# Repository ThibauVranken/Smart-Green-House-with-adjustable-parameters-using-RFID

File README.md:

# Smart-Green-House-with-adjustable-parameters-using-RFID

In this project, you will see how to make your own smart greenhouse with customisable parameters using RFID. The measured sensor values are nicely displayed in a Grafana dashboard via a Grafana server.  You can use this in the industry, for example, to reduce costs in terms of actuator energy or to get a better picture of the situation your plants are in. This way, the plants will always have the ideal environment so they grow faster and healthier.

Folder ‘Documentation + tutorial’:
All hardware and software are in the document ‘Documentatie Serre’ and the explanation to set up a Grafana server is in the document ‘Grafana server’.

Folder ‘Code’:
The code for the ESP32 and the RaspberryPi (MQTT - InfluxDB bridge) are both in this folder.

Folder ‘PCB’:
Here you will find the electronic schematic and pcb design. For more explanation of the circuits, please see ‘Documentatie Serre’.

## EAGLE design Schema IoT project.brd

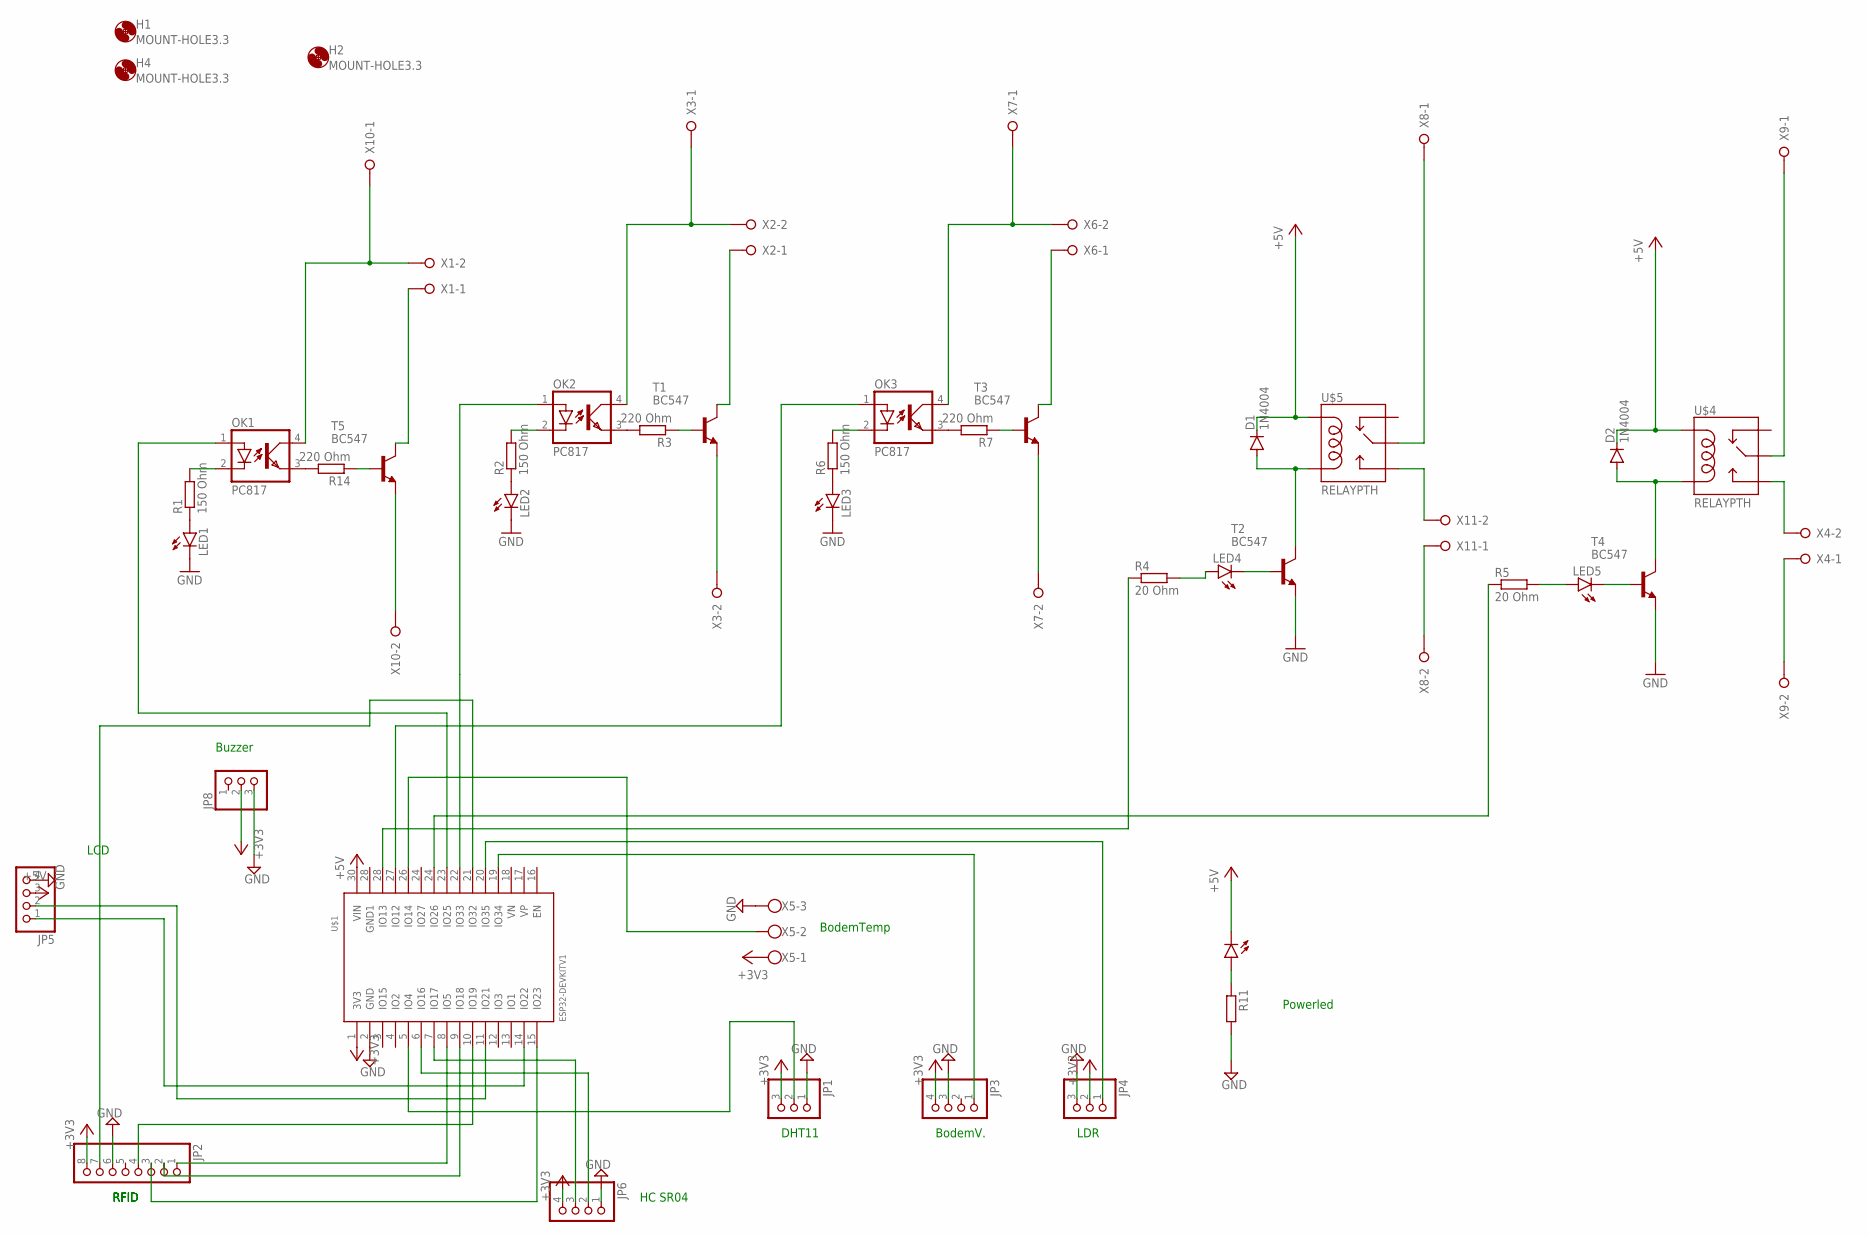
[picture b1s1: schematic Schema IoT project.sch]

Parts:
D1, D2: 1N4004; DO41-10
H1, H2, H4: MOUNT-HOLE3.3; 3,3
JP1, JP4, JP8: PINHD-1X3; 1X03
JP2: PINHD-1X8; 1X08
JP3, JP5, JP6: PINHD-1X4; 1X04
LED1, LED2, LED3, LED4, LED5: LED5MM
OK1, OK2, OK3: PC817; DIL04
PWRLEDRASPBERRYPI2: LED5MM
R1, R2, R6: 150 Ohm; 0207/10
R3, R7, R14: 220 Ohm; 0207/10
R4, R5: 20 Ohm; 0207/10
R11: R-EU_0207/10; 0207/10
T1, T2, T3, T4, T5: BC547; TO92
U$1: ESP32DEVKITV1; ESP32-DEVKITV1
U$4, U$5: RELAYPTH; SRD-05VDC-SL-C
X1, X2, X3, X4, X6, X7, X8, X9, X10, X11: W237-02P; W237-132
X5: W237-103

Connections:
+3V3: JP1.3, JP2.8, JP3.4, JP4.2, JP6.4, JP8.2, U$1.1 (3V3), X5.1
+5V: D1.C, D2.C, JP5.3, PWRLEDRASPBERRYPI2.K (C), U$1.30 (VIN), U$4.COIL1, U$5.COIL1
GND: JP1.1, JP2.6, JP3.3, JP4.3, JP5.4, JP6.1, JP8.3, LED1.K (C), LED2.K (C), LED3.K (C), R11.2, T2.1 (E), T4.1 (E), U$1.2 (GND), X5.3
unnamed: OK1.4 (COL), X1.2, X10.1
unnamed: LED2.A, R2.1
unnamed: D1.A, T2.3 (C), U$5.COIL0
unnamed: OK2.4 (COL), X2.2, X3.1
unnamed: OK1.3 (EMIT), R14.2
unnamed: OK2.3 (EMIT), R3.2
unnamed: R3.1, T1.2 (B)
unnamed: T1.3 (C), X2.1
unnamed: D2.A, T4.3 (C), U$4.COIL0
unnamed: JP3.1, U$1.19 (IO34)
unnamed: LED1.A, R1.1
unnamed: R14.1, T5.2 (B)
unnamed: T1.1 (E), X3.2
unnamed: PWRLEDRASPBERRYPI2.A, R11.1
unnamed: OK2.2 (C), R2.2
unnamed: T5.3 (C), X1.1
unnamed: LED4.K (C), T2.2 (B)
unnamed: R5.1, U$1.24 (IO27)
unnamed: LED4.A, R4.2
unnamed: T5.1 (E), X10.2
unnamed: JP5.2, U$1.11 (IO21)
unnamed: LED3.A, R6.1
unnamed: OK3.1 (A), U$1.27 (IO12)
unnamed: U$4.SWCOMMON, X9.1
unnamed: U$5.SWCOMMON, X8.1
unnamed: OK1.2 (C), R1.2
unnamed: R4.1, U$1.28 (IO13)
unnamed: OK3.4 (COL), X6.2, X7.1
unnamed: OK3.3 (EMIT), R7.2
unnamed: X8.2, X11.1
unnamed: U$1.26 (IO14), X5.2
unnamed: JP6.3, U$1.7 (IO17)
unnamed: JP4.1, U$1.20 (IO35)
unnamed: JP2.7, U$1.21 (IO32)
unnamed: JP2.4, U$1.10 (IO19)
unnamed: JP6.2, U$1.6 (IO16)
unnamed: R7.1, T3.2 (B)
unnamed: JP1.2, U$1.5 (IO4)
unnamed: JP5.1, U$1.14 (IO22)
unnamed: T3.3 (C), X6.1
unnamed: U$5.SWOPEN, X11.2
unnamed: U$4.SWOPEN, X4.2
unnamed: T3.1 (E), X7.2
unnamed: OK3.2 (C), R6.2
unnamed: X4.1, X9.2
unnamed: LED5.A, R5.2
unnamed: LED5.K (C), T4.2 (B)
unnamed: JP2.3, U$1.15 (IO23)
unnamed: JP2.2, U$1.9 (IO18)
unnamed: JP2.1, U$1.8 (IO5)
unnamed: OK1.1 (A), U$1.23 (IO25)

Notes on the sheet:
DHT11
BodemV.
LDR
BodemTemp
RFID
HC SR04
LCD
Powerled
Buzzer

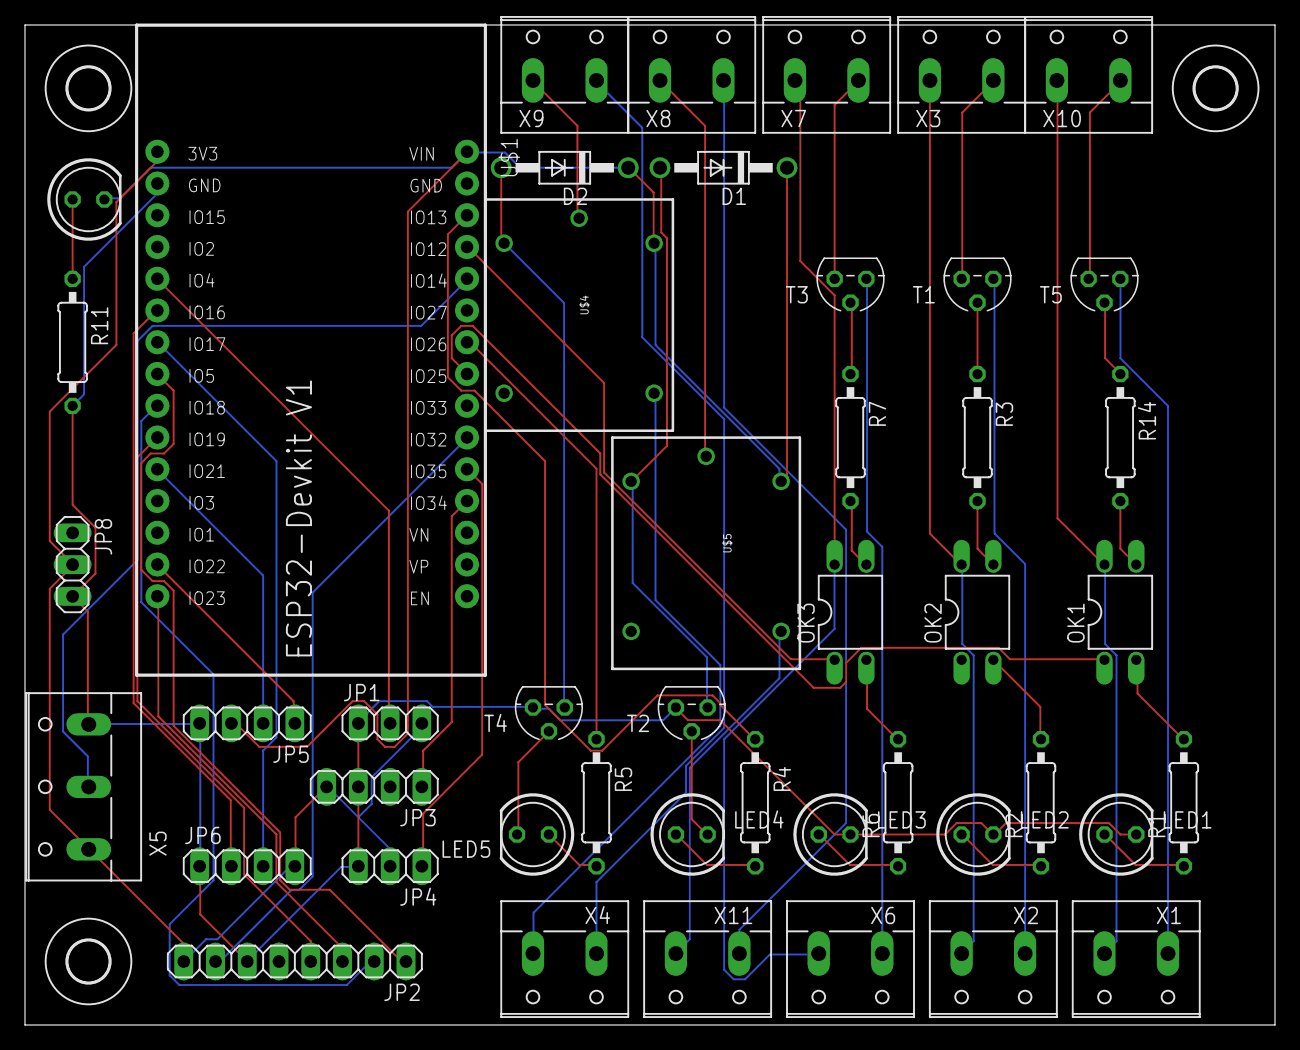
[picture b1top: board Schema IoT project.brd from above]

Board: 2 copper layers, 100.0 x 80.0 mm, 49 parts (0 on the bottom side), 54 nets.
